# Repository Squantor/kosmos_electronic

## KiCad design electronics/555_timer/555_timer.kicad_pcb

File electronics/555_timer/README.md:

# 555 timer module
555 timer module
## BOM
* The X1000 and XN1000 special pins for the connections, I have found something similar by [Mill-max 6092](https://www.mill-max.com/catalog/download/2020-10%3A207M.pdf) available at [digikey](https://www.digikey.com/en/products/detail/mill-max-manufacturing-corp/6092-0-00-15-00-00-33-0/1991698)

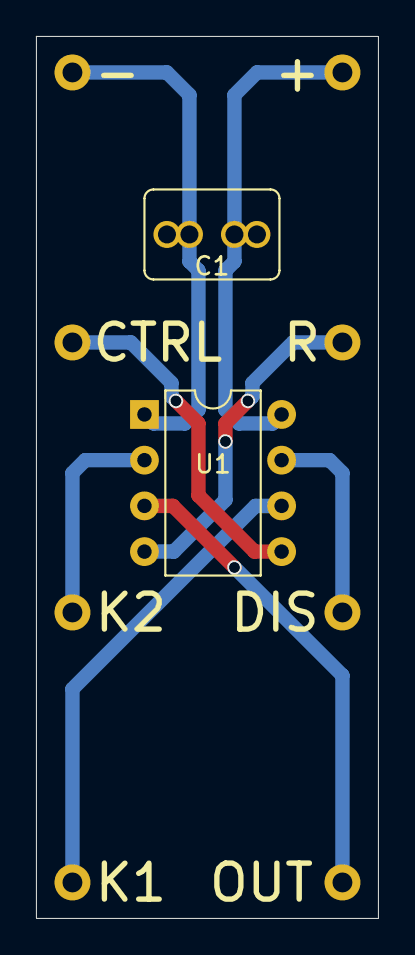
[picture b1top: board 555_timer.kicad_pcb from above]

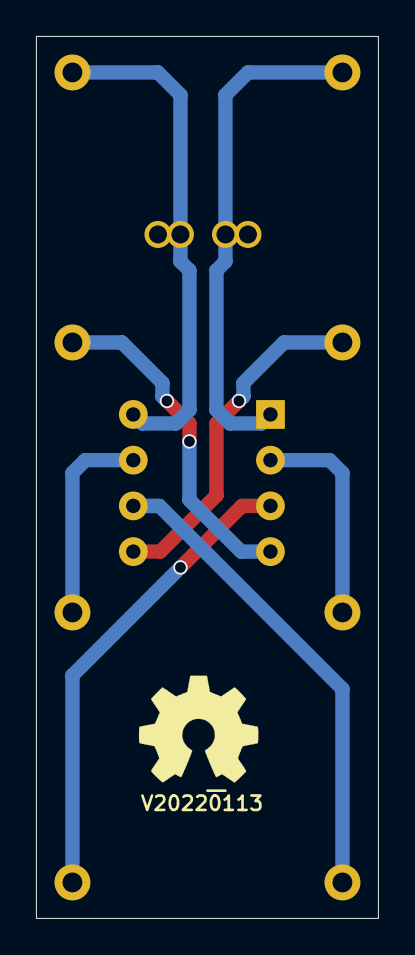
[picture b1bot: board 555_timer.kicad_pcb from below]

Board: 2 copper layers, 19.0 x 49.0 mm, 12 parts (2 on the bottom side), 8 nets.

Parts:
C1: 470n; C-025_050-050X100
J1: -; PC_pin_nail_head_6092
J2: CTRL; PC_pin_nail_head_6092
J3: K2; PC_pin_nail_head_6092
J4: K1; PC_pin_nail_head_6092
J5: OUT; PC_pin_nail_head_6092
J6: DIS; PC_pin_nail_head_6092
J7: R; PC_pin_nail_head_6092
J8: +; PC_pin_nail_head_6092
N1: V20220113; Label_Generic
N2: OHWLOGO; OSHW-Symbol_6.7x6mm_SilkScreen
U1: NE555_timer; DIP-8_W7.62mm

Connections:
unnamed: C1.1, J8.1, U1.8
unnamed: C1.2, J1.1, U1.1
unnamed: J2.1, U1.5
unnamed: J3.1, U1.2
unnamed: J4.1, U1.6
unnamed: J5.1, U1.3
unnamed: J6.1, U1.7
unnamed: J7.1, U1.4

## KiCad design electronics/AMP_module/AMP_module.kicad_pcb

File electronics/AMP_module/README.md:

# Amplifier module
Copy of the AMP module found in the X2000 and XN2000 electronics boxes. This module is a TBA820M speaker amplifier with decoupling capacitor, [boucherot cell](https://en.wikipedia.org/wiki/Boucherot_cell) and boost cap.
## BOM
* The X1000 and XN1000 special pins for the connections, I have found something similar by [Mill-max 6092](https://www.mill-max.com/catalog/download/2020-10%3A207M.pdf) available at [digikey](https://www.digikey.com/en/products/detail/mill-max-manufacturing-corp/6092-0-00-15-00-00-33-0/1991698)
* [TBA820ML-D08-T by UTC](https://lcsc.com/product-detail/Audio-Power-OpAmps_UTC-Unisonic-Tech-TBA820ML-D08-T_C171467.html)

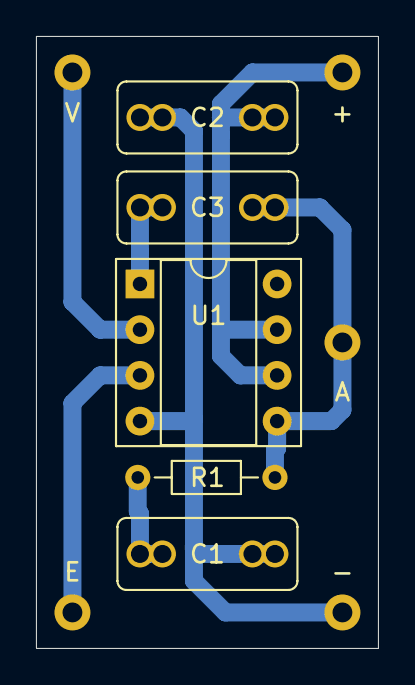
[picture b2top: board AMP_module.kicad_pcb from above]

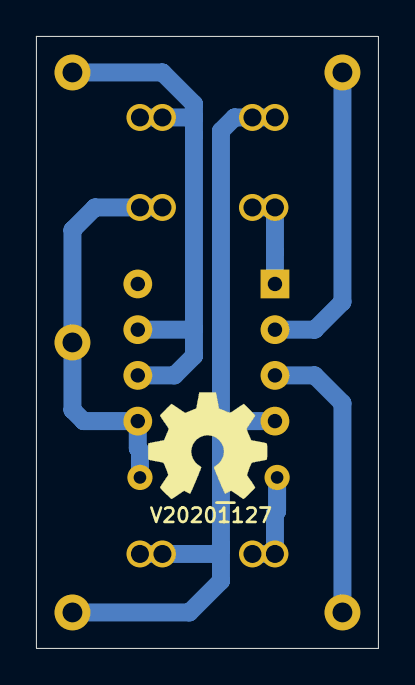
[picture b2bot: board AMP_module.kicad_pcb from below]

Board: 2 copper layers, 19.0 x 34.0 mm, 12 parts (2 on the bottom side), 7 nets.

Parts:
C1, C2: 330n; C-050_075-040X100
C3: 330p; C-050_075-040X100
J1: V; PC_pin_nail_head_6092
J3: E; PC_pin_nail_head_6092
J4: -; PC_pin_nail_head_6092
J5: A; PC_pin_nail_head_6092
J6: +; PC_pin_nail_head_6092
N1: V20201127; Label_Generic
N2: OHWLOGO; OSHW-Symbol_6.7x6mm_SilkScreen
R1: 1; R_Axial_DIN0204_L3.6mm_D1.6mm_P7.62mm_Horizontal
U1: TBA820M; DIP-8_W7.62mm_Socket

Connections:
/GND: C1.2, C2.2, J4.1, U1.4
/VCC: C2.1, J6.1, U1.6, U1.7
unnamed: C1.1, R1.2
unnamed: C3.1, J5.1, R1.1, U1.5
unnamed: C3.2, U1.1
unnamed: J1.1, U1.2
unnamed: J3.1, U1.3

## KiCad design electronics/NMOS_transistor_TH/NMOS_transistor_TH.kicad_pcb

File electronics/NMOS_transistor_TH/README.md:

# Kosmos electronic NMOS transistor
Kosmos electronic NMOS transistor module
## TODO's
Still some things need to be done:
* Manufacturing
* Test
* Pictures
## BOM
* Kosmos electronic uses some special pins for the connections, I have found something similar by [Mill-max 6092](https://www.mill-max.com/catalog/download/2020-10%3A207M.pdf) available at [digikey](https://www.digikey.com/en/products/detail/mill-max-manufacturing-corp/6092-0-00-15-00-00-33-0/1991698)
* BS170 style NMOS transistor

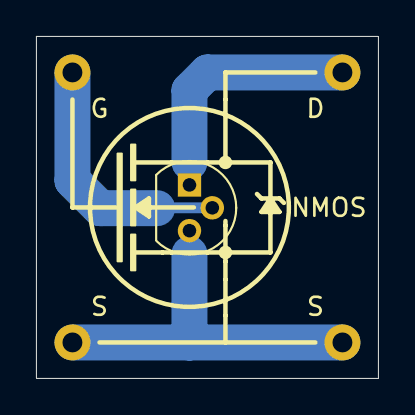
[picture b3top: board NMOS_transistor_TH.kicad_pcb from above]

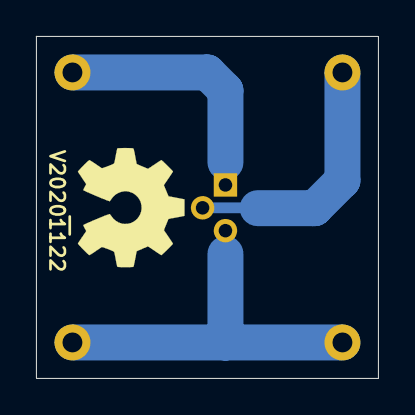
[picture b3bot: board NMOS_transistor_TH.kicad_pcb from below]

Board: 2 copper layers, 19.0 x 19.0 mm, 7 parts (2 on the bottom side), 3 nets.

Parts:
J1: G; PC_pin_nail_head_6092
J2, J4: S; PC_pin_nail_head_6092
J3: D; PC_pin_nail_head_6092
N1: V20201122; Label_Generic
N2: OHWLOGO; OSHW-Symbol_6.7x6mm_SilkScreen
Q1: Q_NMOS_DGS; TO-92

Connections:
unnamed: J1.1, Q1.2
unnamed: J2.1, J4.1, Q1.3
unnamed: J3.1, Q1.1

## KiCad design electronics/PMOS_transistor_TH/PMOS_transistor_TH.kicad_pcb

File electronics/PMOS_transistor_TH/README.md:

# Kosmos electronic PMOS transistor
Kosmos electronic PMOS transistor module
## TODO's
Still some things need to be done:
* Manufacturing
* Test
* Pictures
## BOM
* Kosmos electronic uses some special pins for the connections, I have found something similar by [Mill-max 6092](https://www.mill-max.com/catalog/download/2020-10%3A207M.pdf) available at [digikey](https://www.digikey.com/en/products/detail/mill-max-manufacturing-corp/6092-0-00-15-00-00-33-0/1991698)
* BS250 style NMOS transistor

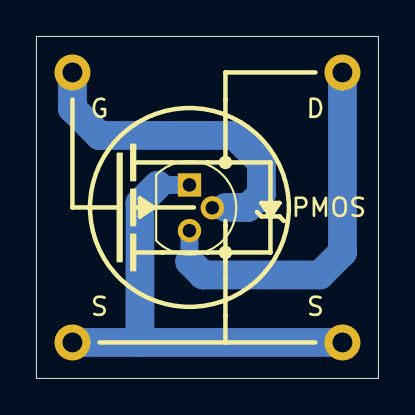
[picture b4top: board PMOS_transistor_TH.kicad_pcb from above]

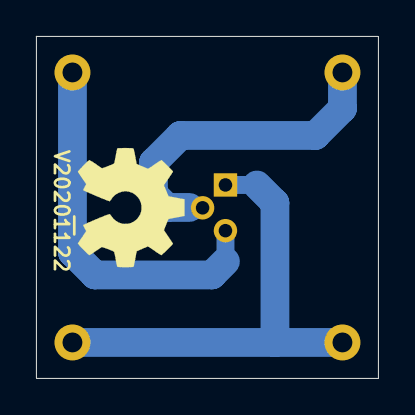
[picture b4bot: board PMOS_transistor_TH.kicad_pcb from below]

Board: 2 copper layers, 19.0 x 19.0 mm, 7 parts (2 on the bottom side), 3 nets.

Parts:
J1: G; PC_pin_nail_head_6092
J2, J4: S; PC_pin_nail_head_6092
J3: D; PC_pin_nail_head_6092
N1: V20201122; Label_Generic
N2: OHWLOGO; OSHW-Symbol_6.7x6mm_SilkScreen
Q1: Q_PMOS_SGD; TO-92

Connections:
unnamed: J1.1, Q1.2
unnamed: J2.1, J4.1, Q1.1
unnamed: J3.1, Q1.3
